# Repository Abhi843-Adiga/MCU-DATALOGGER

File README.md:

MCU Data Logger (2-Layer & 4-Layer PCB Design) :        
-> A compact, modular microcontroller-based data logger designed using KiCad.         
-> This project includes both 2-layer and 4-layer PCB implementations managed through Git branching and git attributes.

Design Disclaimer :
These PCB designs are provided for educational purposes only.

Passed Checks:
The designs have successfully passed basic ERC (Electrical Rules Check) and DRC (Design Rule Check) in the KICAD.

Untested Aspects:
These designs have not been validated for advanced electrical performance.
Critical aspects that have not been analyzed or tested include:
->Signal Integrity (SI):High-speed signals (like SPI) have not been analyzed for reflections or timing issues.
->Power Integrity (PI):The power delivery network has not been simulated for stability.
->EMI/EMC:The design has not been tested for electromagnetic interference or compatibility. 

It will likely not pass regulatory certifications without further revisions.

Do not use these designs for a production-ready or commercial product without performing a thorough analysis and validation for SI, PI, and EMC.

Contributing:
If you have experience in SI/PI analysis, EMC hardening, or would like to improve the design, please feel free to fork the repository and submit a pull request.

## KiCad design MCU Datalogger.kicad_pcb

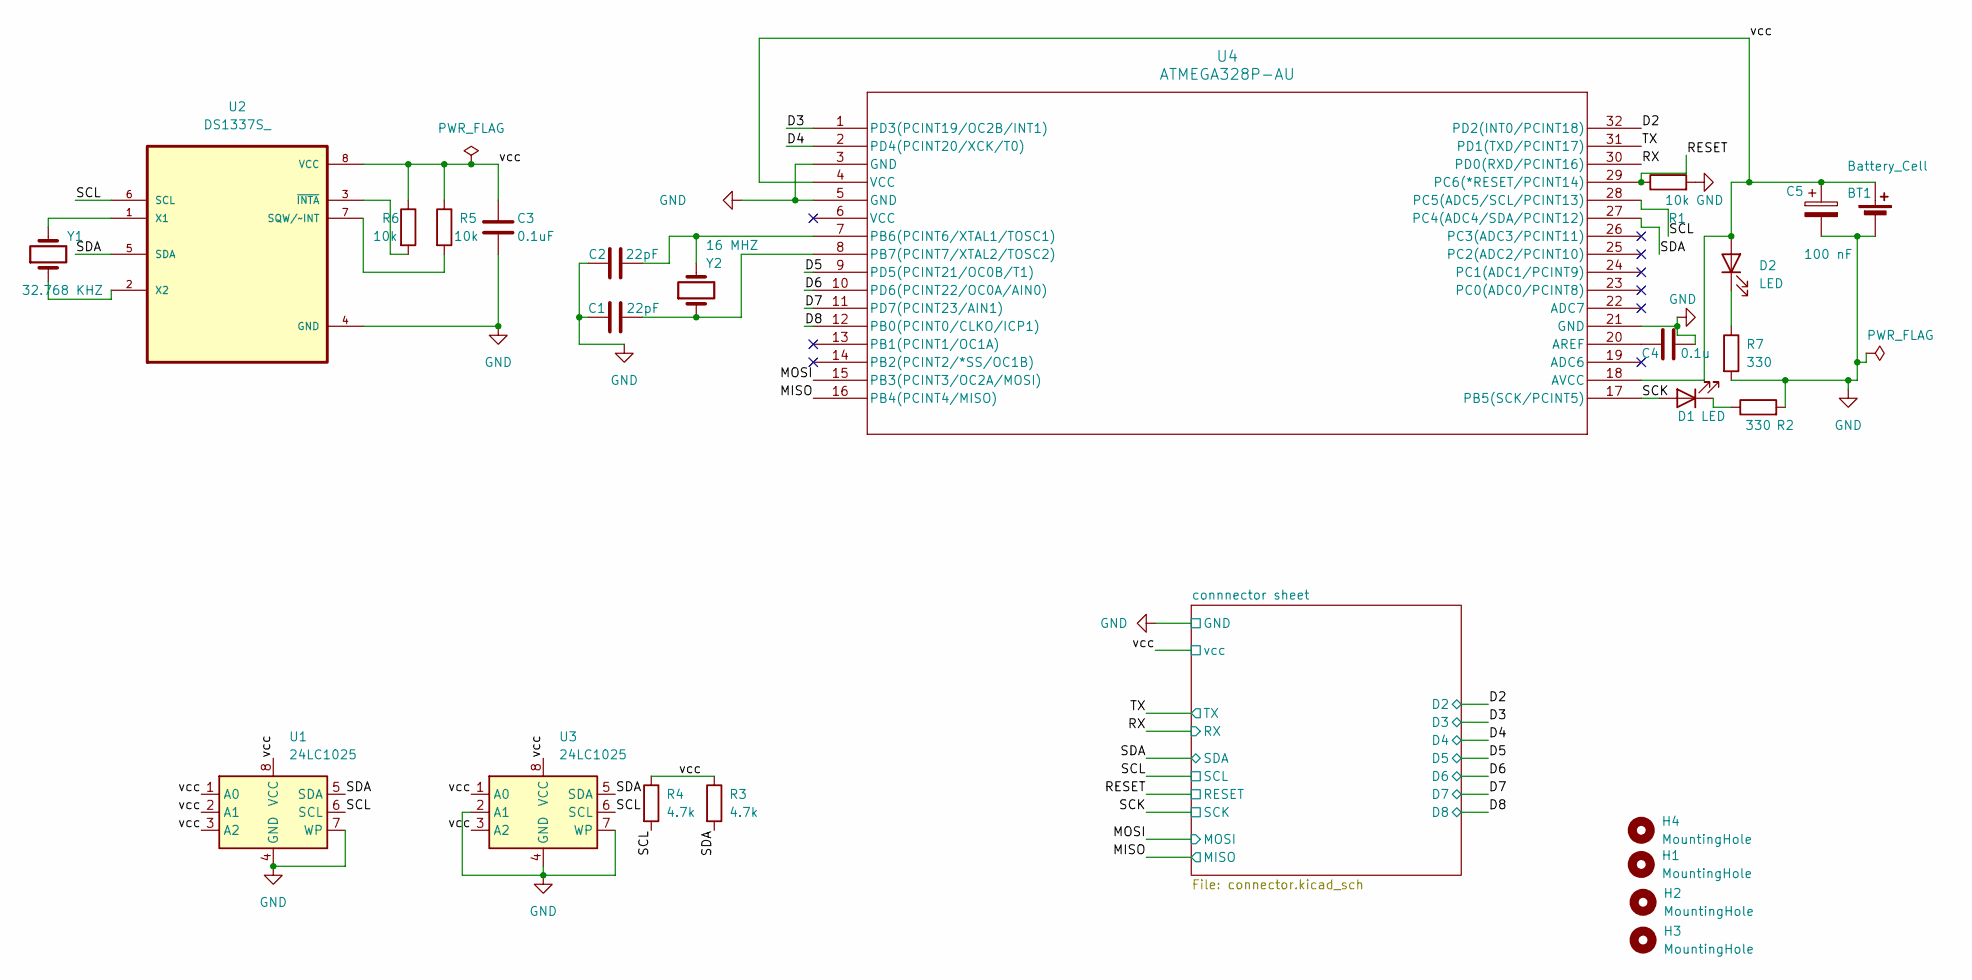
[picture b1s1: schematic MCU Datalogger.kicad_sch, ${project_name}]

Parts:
BT1: Battery_Cell; PinHeader_1x02_P2.54mm_Vertical
C1, C2: 22pF; C_0805_2012Metric
C3: 0.1uF; C_0805_2012Metric
C4: 0.1u; C_0805_2012Metric
C5: 100 nF; CP_Elec_3x5.3
D1, D2: LED; LED_0805_2012Metric
H1, H2, H3, H4: MountingHole; MountingHole_2.1mm
R1, R5, R6: 10k; R_0805_2012Metric
R2, R7: 330; R_0805_2012Metric
R3, R4: 4.7k; R_0805_2012Metric
U1, U3: 24LC1025; SOIC-8_3.9x4.9mm_P1.27mm
U2: DS1337S_; SOIC127P600X175-8N
U4: ATMEGA328P-AU; TQFP32_32A_MCH
Y1: 32.768 KHZ; Crystal_SMD_5032-2Pin_5.0x3.2mm_HandSoldering
Y2: 16 MHZ; Crystal_SMD_5032-2Pin_5.0x3.2mm_HandSoldering

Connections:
/D2: U4.32 (PD2(INT0/PCINT18)); also elsewhere on the board
/D3: U4.1 (PD3(PCINT19/OC2B/INT1)); also elsewhere on the board
/D4: U4.2 (PD4(PCINT20/XCK/T0)); also elsewhere on the board
/D5: U4.9 (PD5(PCINT21/OC0B/T1)); also elsewhere on the board
/D6: U4.10 (PD6(PCINT22/OC0A/AIN0)); also elsewhere on the board
/D7: U4.11 (PD7(PCINT23/AIN1)); also elsewhere on the board
/D8: U4.12 (PB0(PCINT0/CLKO/ICP1)); also elsewhere on the board
/MISO: U4.16 (PB4(PCINT4/MISO)); also elsewhere on the board
/MOSI: U4.15 (PB3(PCINT3/OC2A/MOSI)); also elsewhere on the board
/RESET: R1.1, U4.29 (PC6(*RESET/PCINT14)); also elsewhere on the board
/RX: U4.30 (PD0(RXD/PCINT16)); also elsewhere on the board
/SCK: D1.2 (A), U4.17 (PB5(SCK/PCINT5)); also elsewhere on the board
/SCL: R4.2, U1.6 (SCL), U2.6 (SCL), U3.6 (SCL), U4.28 (PC5(ADC5/SCL/PCINT13)); also elsewhere on the board
/SDA: R3.2, U1.5 (SDA), U2.5 (SDA), U3.5 (SDA), U4.27 (PC4(ADC4/SDA/PCINT12)); also elsewhere on the board
/TX: U4.31 (PD1(TXD/PCINT17)); also elsewhere on the board
/vcc: BT1.1 (+), C3.1, C5.1, D2.2 (A), R3.1, R4.1, R5.1, R6.1, U1.1 (A0), U1.2 (A1), U1.3 (A2), U1.8 (VCC), U2.8 (VCC), U3.1 (A0), U3.3 (A2), U3.8 (VCC), U4.4 (VCC), U4.18 (AVCC); also elsewhere on the board
GND: BT1.2 (-), C1.1, C2.1, C3.2, C4.2, C5.2, R1.2, R2.2, R7.2, U1.4 (GND), U1.7 (WP), U2.4 (GND), U3.2 (A1), U3.4 (GND), U3.7 (WP), U4.3 (GND), U4.5 (GND), U4.21 (GND); also elsewhere on the board
unnamed: D1.1 (K), R2.1
unnamed: D2.1 (K), R7.1
unnamed: R5.2, U2.7 (SQW/~INT)
unnamed: U2.1 (X1), Y1.2
unnamed: U2.2 (X2), Y1.1
unnamed: R6.2, U2.3 (~INTA)
unnamed: C4.1, U4.20 (AREF)
unnamed: C2.2, U4.7 (PB6(PCINT6/XTAL1/TOSC1)), Y2.2
unnamed: C1.2, U4.8 (PB7(PCINT7/XTAL2/TOSC2)), Y2.1

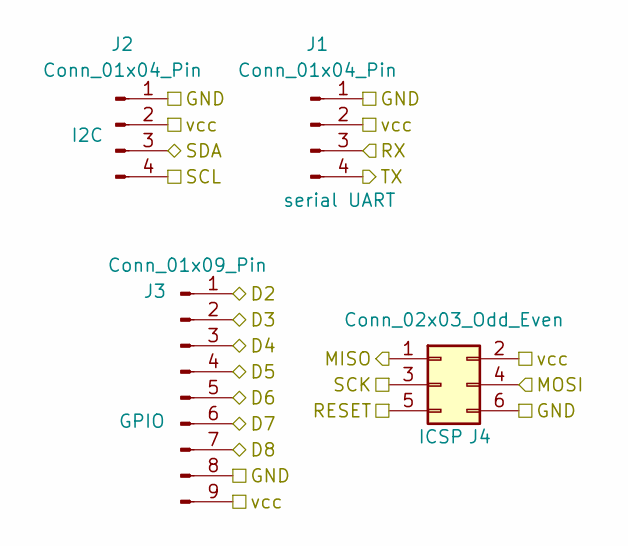
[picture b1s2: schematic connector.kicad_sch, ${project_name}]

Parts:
J1, J2: Conn_01x04_Pin; PinHeader_1x04_P2.54mm_Vertical
J3: Conn_01x09_Pin; PinHeader_1x09_P2.54mm_Vertical
J4: Conn_02x03_Odd_Even; PinHeader_2x03_P2.54mm_Vertical

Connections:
/D2: J3.1; also elsewhere on the board
/D3: J3.2; also elsewhere on the board
/D4: J3.3; also elsewhere on the board
/D5: J3.4; also elsewhere on the board
/D6: J3.5; also elsewhere on the board
/D7: J3.6; also elsewhere on the board
/D8: J3.7; also elsewhere on the board
/MISO: J4.1; also elsewhere on the board
/MOSI: J4.4; also elsewhere on the board
/RESET: J4.5; also elsewhere on the board
/RX: J1.3; also elsewhere on the board
/SCK: J4.3; also elsewhere on the board
/SCL: J2.4; also elsewhere on the board
/SDA: J2.3; also elsewhere on the board
/TX: J1.4; also elsewhere on the board
/vcc: J1.2, J2.2, J3.9, J4.2; also elsewhere on the board
GND: J1.1, J2.1, J3.8, J4.6; also elsewhere on the board

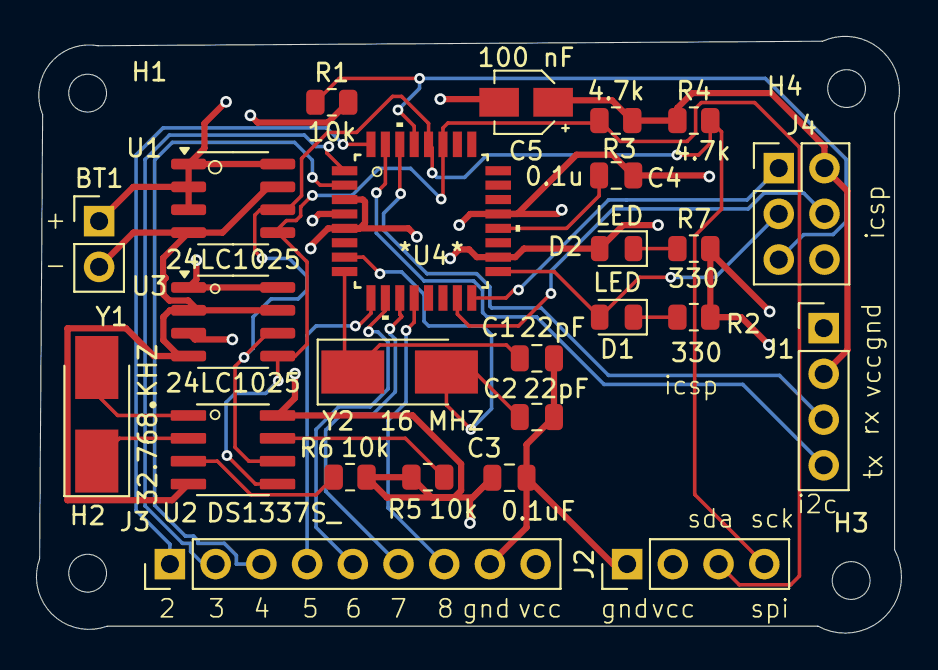
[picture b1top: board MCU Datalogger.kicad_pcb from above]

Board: 4 copper layers, 48.1 x 33.1 mm, 29 parts (0 on the bottom side), 26 nets.

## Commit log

2025-06-18 Setup of EESchema
2025-06-19 symbols initialized
2025-06-19 symbols updated
2025-06-19 symbols arranged
2025-06-19 Added commponent values
2025-06-19 Footprints Associated
2025-06-19 Wiring of first sheet
2025-06-19 COMPLETED THE WIRING AND RESOLVED ERC ERRORS SUCH AS POWER PIN ASSIGNMENT AND THE MCU UNIT SYMBOL TYPE(INPUT,OUTPUT,PASSIVE ETC
2025-06-19 completion of schematic
2025-06-19 setup of pcbnew
2025-06-19 placed components
2025-06-19 Routing done and fixed the drc errors successfully
2025-06-20 copper fill and drc and refining the edge cuts completed
2025-06-20 arranged route tracks
2025-06-20 arranged route track and later the schematics there was small mistkae so arranged and routed successfully preparation for manufacturing
2025-06-20 completed full pcb 2 layer MCU datalogger
2025-06-20 completed full pcb 4 layer MCU datalogger
2025-06-20 completed full pcb 4 layer MCU datalogger by debugging it
2025-06-20 Added git attributes file to prevent merge from main
2025-06-20 added some info
2025-06-21 added info
2025-06-23 fixed two defects in schematic
2025-06-23 updated 2layer pcb
2025-06-23 updated 4layer pcb
